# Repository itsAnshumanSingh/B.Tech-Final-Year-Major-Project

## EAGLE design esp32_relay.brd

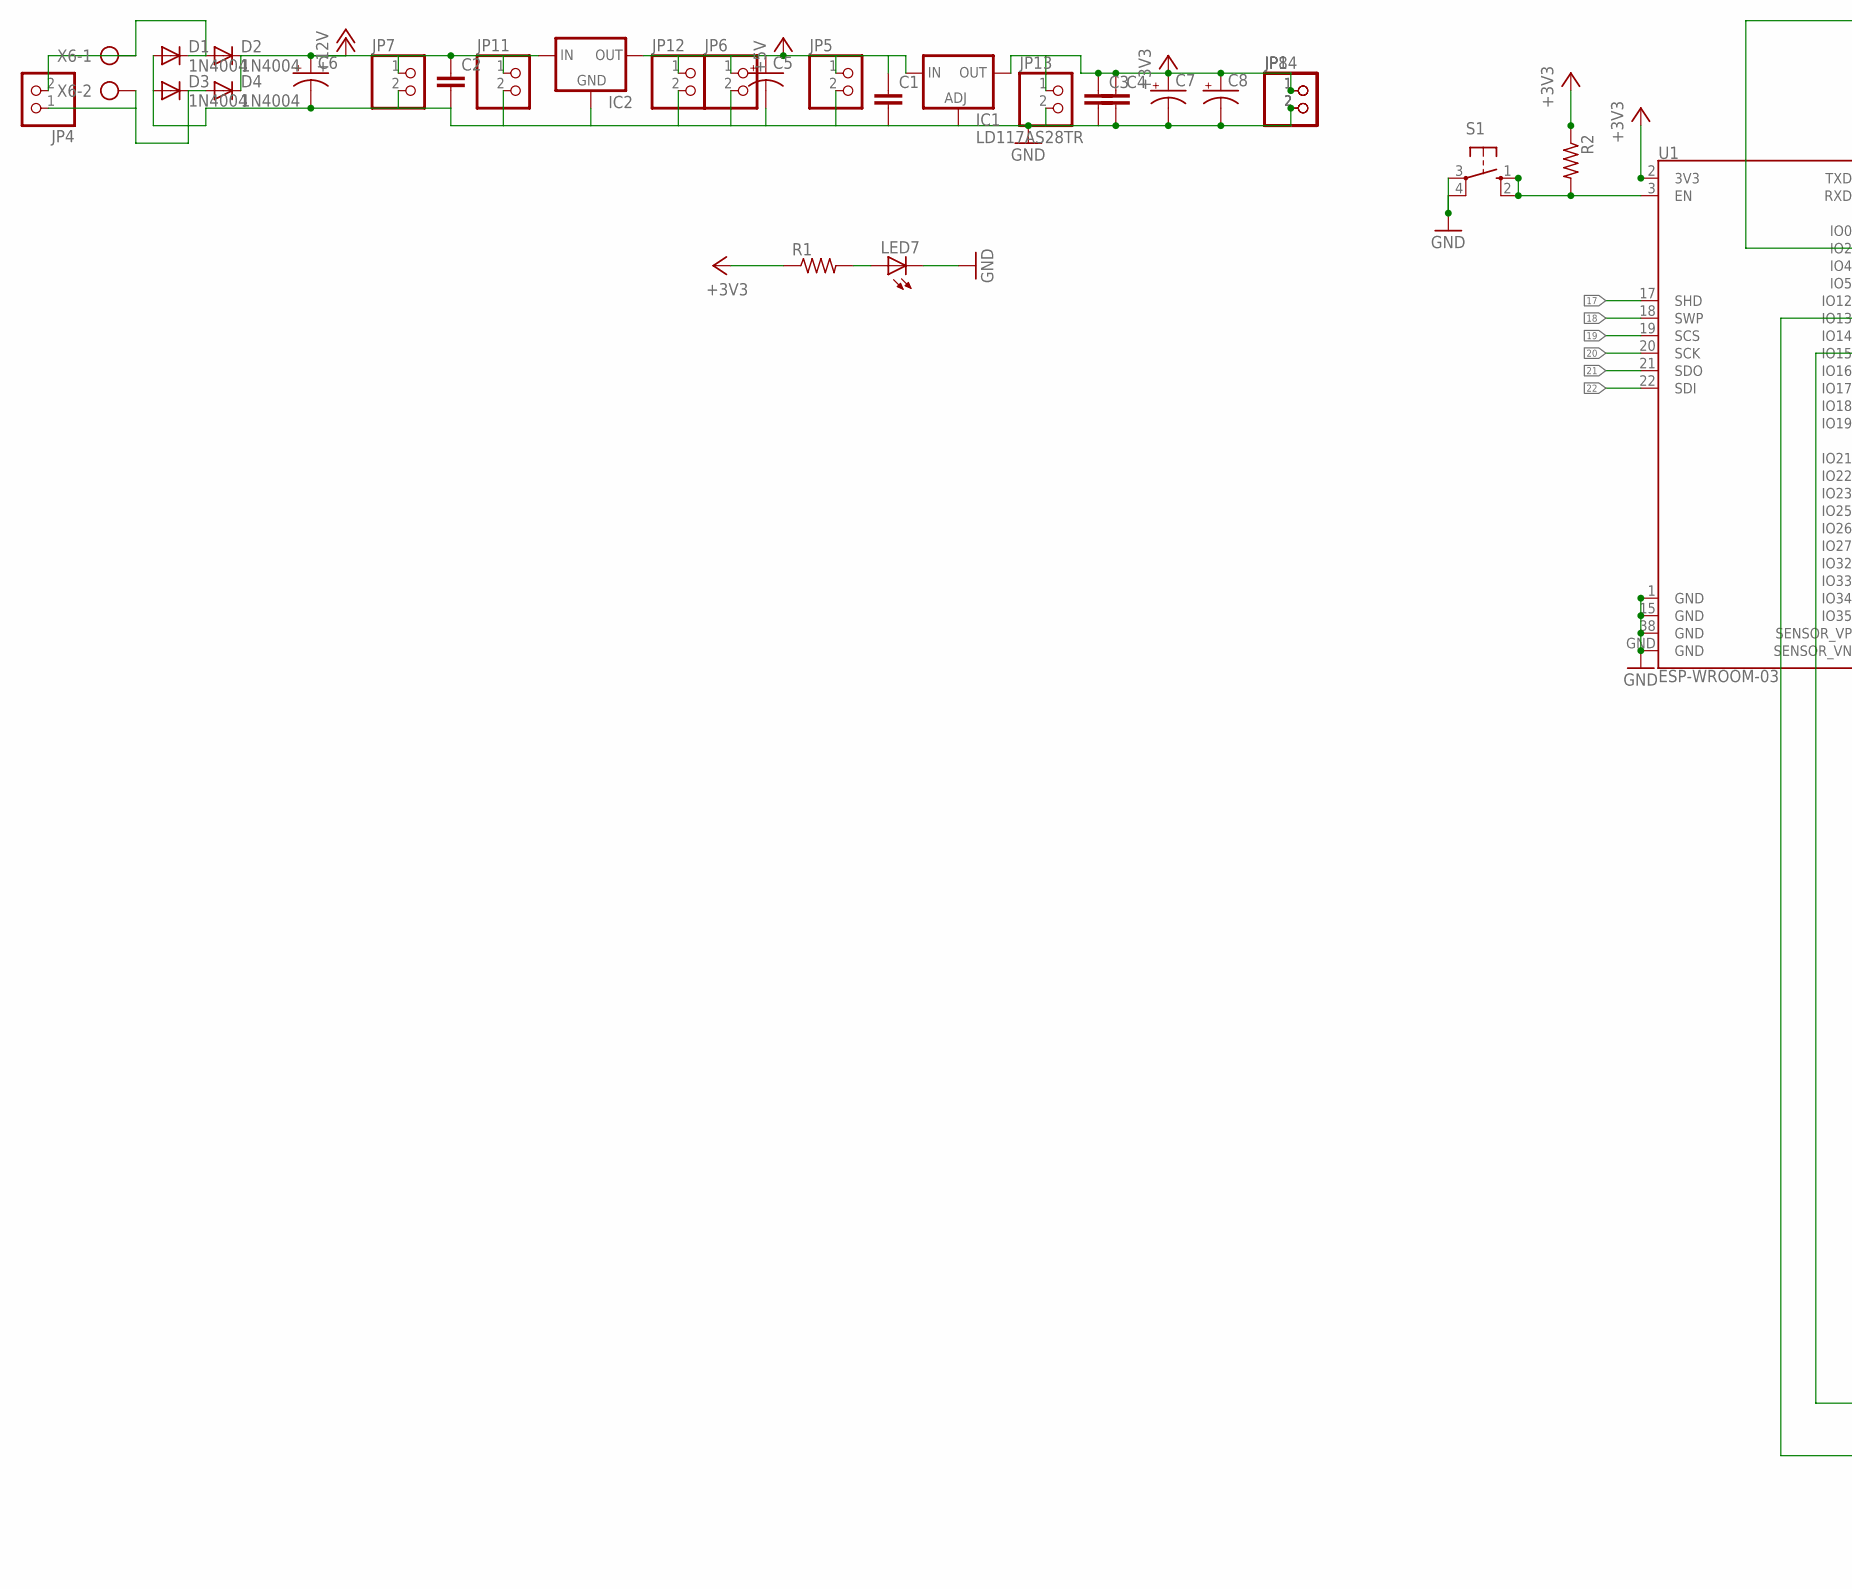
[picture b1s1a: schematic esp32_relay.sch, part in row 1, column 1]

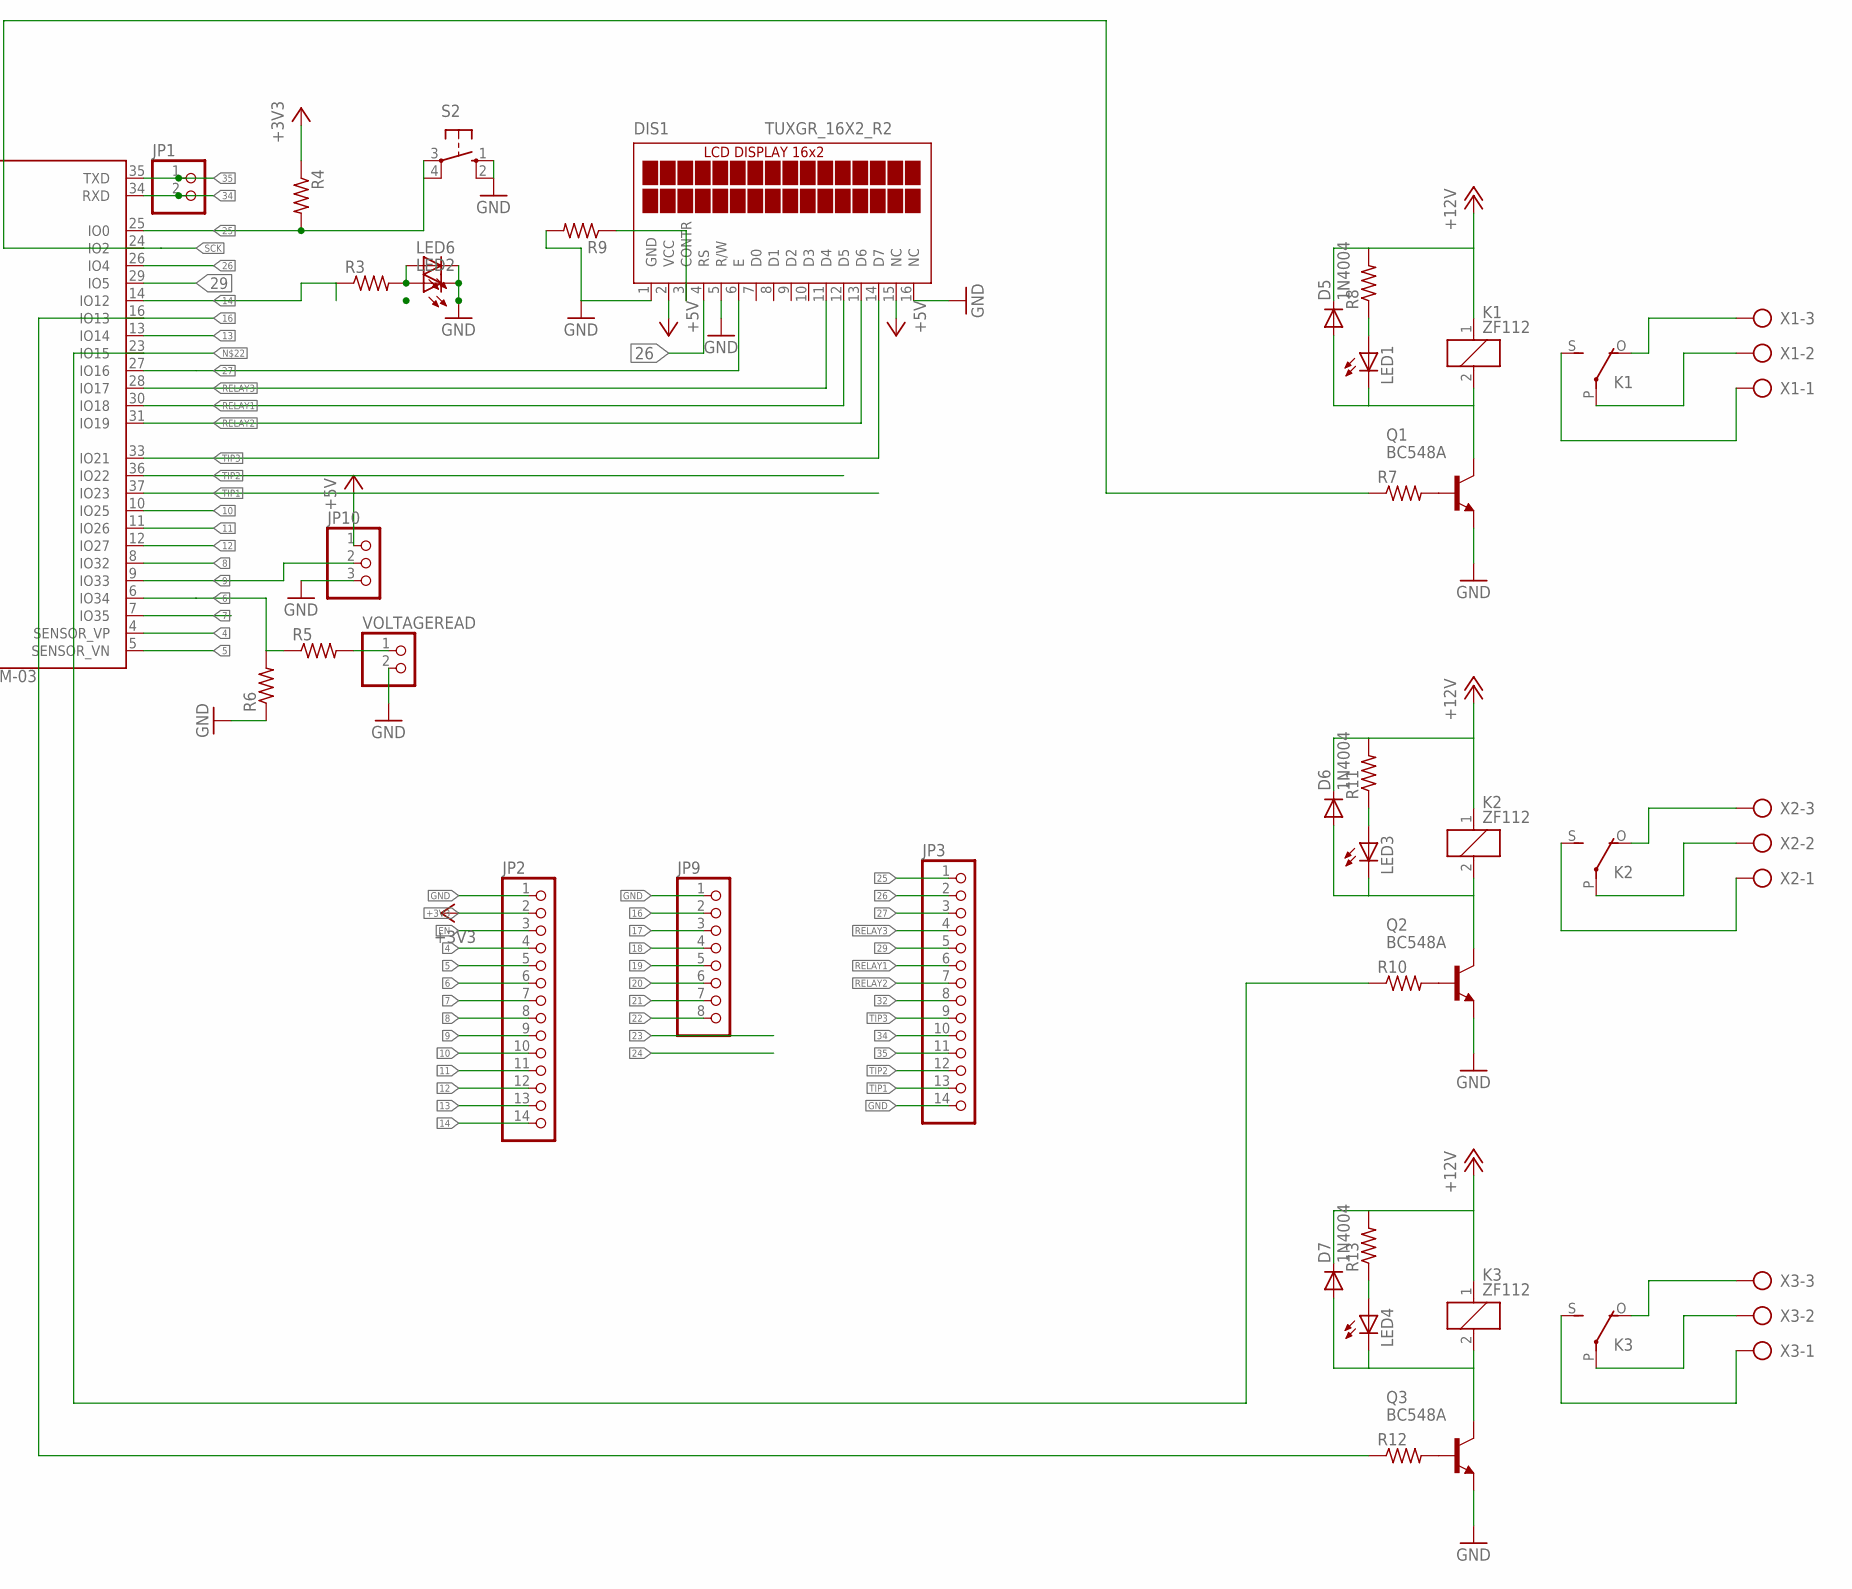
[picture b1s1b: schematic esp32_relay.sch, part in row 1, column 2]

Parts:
C1, C2, C3, C4: C-EUC1206; C1206
C5, C6, C8: CPOL-USE2.5-7; E2,5-7
C7: CPOL-USE2.5-6; E2,5-6
D1, D2, D3, D4, D5, D6, D7: 1N4004; DO41-10
DIS1: TUXGR_16X2_R2
IC1: LD117AS28TR; SOT223
IC2: 78XXL
JP1, JP4, JP5, JP6, JP7, JP8, JP11, JP12, JP13, JP14: PINHD-1X2; 1X02
JP2, JP3: PINHD-1X14; 1X14
JP9: PINHD-1X8; 1X08
JP10: PINHD-1X3; 1X03
K1, K2, K3: ZF112
LED1, LED3, LED4, LED6, LED7: LED3MM
LED2: LEDCHIPLED_1206; CHIPLED_1206
Q1, Q2, Q3: BC548A; TO92-EBC
R1, R2, R3, R4, R5, R6, R7, R8, R9, R10, R11, R13: R-US_0207/7; 0207/7
R12: R-US_0207/10; 0207/10
S1, S2: 10-XX; B3F-10XX
U1: ESP-WROOM-03
VOLTAGEREAD: PINHD-1X2; 1X02
X1, X2, X3: AK500/3-H
X6: AK500/2-H

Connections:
4: JP2.4, U1.4 (SENSOR_VP)
5: JP2.5, U1.5 (SENSOR_VN)
6: JP2.6, R5.1, R6.2, U1.6 (IO34)
7: JP2.7, U1.7 (IO35)
8: JP2.8, U1.8 (IO32)
9: JP2.9, JP10.2, U1.9 (IO33)
10: JP2.10, U1.10 (IO25)
11: JP2.11, U1.11 (IO26)
12: JP2.12, U1.12 (IO27)
13: JP2.13, U1.13 (IO14)
14: JP2.14, R3.1, U1.14 (IO12)
16: JP9.2, R12.1, U1.16 (IO13)
17: JP9.3, U1.17 (SHD)
18: JP9.4, U1.18 (SWP)
19: JP9.5, U1.19 (SCS)
20: JP9.6, U1.20 (SCK)
21: JP9.7, U1.21 (SDO)
22: JP9.8, U1.22 (SDI)
25: JP3.1, R4.2, S2.3, S2.4 (P1), U1.25 (IO0)
26: DIS1.4 (RS), JP3.2, U1.26 (IO4)
27: DIS1.6 (E), JP3.3, U1.27 (IO16)
29: JP3.5, U1.29 (IO5)
32: JP3.8
34: JP1.2, JP3.10, U1.34 (RXD)
35: JP1.1, JP3.11, U1.35 (TXD)
+3V3: C3.1, C4.1, C7.+, C8.+, IC1.4 (OUT), JP2.2, JP8.1, JP13.1, JP14.1, R1.1, R2.1, R4.1, U1.2 (3V3)
+5V: C1.1, C5.+, DIS1.2 (VCC), DIS1.15 (NC), IC1.3 (IN), IC2.OUT, JP5.1, JP6.1, JP10.1, JP12.1
+12V: C2.1, C6.+, D2.C, D4.C, D5.C, D6.C, D7.C, IC2.IN, JP7.1, JP11.1, K1.1, K2.1, K3.1, R8.2, R11.2, R13.2
EN: JP2.3, R2.2, S1.1 (S), S1.2 (S1), U1.3 (EN)
GND: C1.2, C2.2, C3.2, C4.2, C5.-, C6.-, C7.-, C8.-, D1.A, D3.A, DIS1.1 (GND), DIS1.5 (R/W), DIS1.16 (NC), IC1.1 (ADJ), IC2.GND, JP2.1, JP3.14, JP5.2, JP6.2, JP7.2, JP8.2, JP9.1, JP10.3, JP11.2, JP12.2, JP13.2, JP14.2, LED2.C, LED6.K (C), LED7.K (C), Q1.E, Q2.E, Q3.E, R6.1, R9.2, S1.3, S1.4 (P1), S2.1 (S), S2.2 (S1), U1.1 (GND), U1.15 (GND), U1.38 (GND), U1.GND, VOLTAGEREAD.2
unnamed: LED7.A, R1.2
unnamed: D3.C, D4.A, JP4.1, X6.2
unnamed: Q1.B, R7.2
unnamed: R5.2, VOLTAGEREAD.1
unnamed: D5.A, K1.2, LED1.K (C), Q1.C
unnamed: K1.P, X1.2
unnamed: LED2.A, LED6.A, R3.2
unnamed: K1.O, X1.3
unnamed: D1.C, D2.A, JP4.2, X6.1
unnamed: K1.S, X1.1
unnamed: LED1.A, R8.1
unnamed: DIS1.3 (CONTR), R9.1
unnamed: R10.1, U1.23 (IO15)
unnamed: Q2.B, R10.2
unnamed: D6.A, K2.2, LED3.K (C), Q2.C
unnamed: K2.P, X2.2
unnamed: K2.O, X2.3
unnamed: K2.S, X2.1
unnamed: LED3.A, R11.1
unnamed: Q3.B, R12.2
unnamed: D7.A, K3.2, LED4.K (C), Q3.C
unnamed: K3.P, X3.2
unnamed: K3.O, X3.3
unnamed: K3.S, X3.1
unnamed: LED4.A, R13.1
RELAY1: DIS1.12 (D5), JP3.6, U1.30 (IO18)
RELAY2: DIS1.13 (D6), JP3.7, U1.31 (IO19)
RELAY3: DIS1.11 (D4), JP3.4, U1.28 (IO17)
SCK: R7.1, U1.24 (IO2)
TIP1: JP3.13, U1.37 (IO23)
TIP2: JP3.12, U1.36 (IO22)
TIP3: DIS1.14 (D7), JP3.9, U1.33 (IO21)

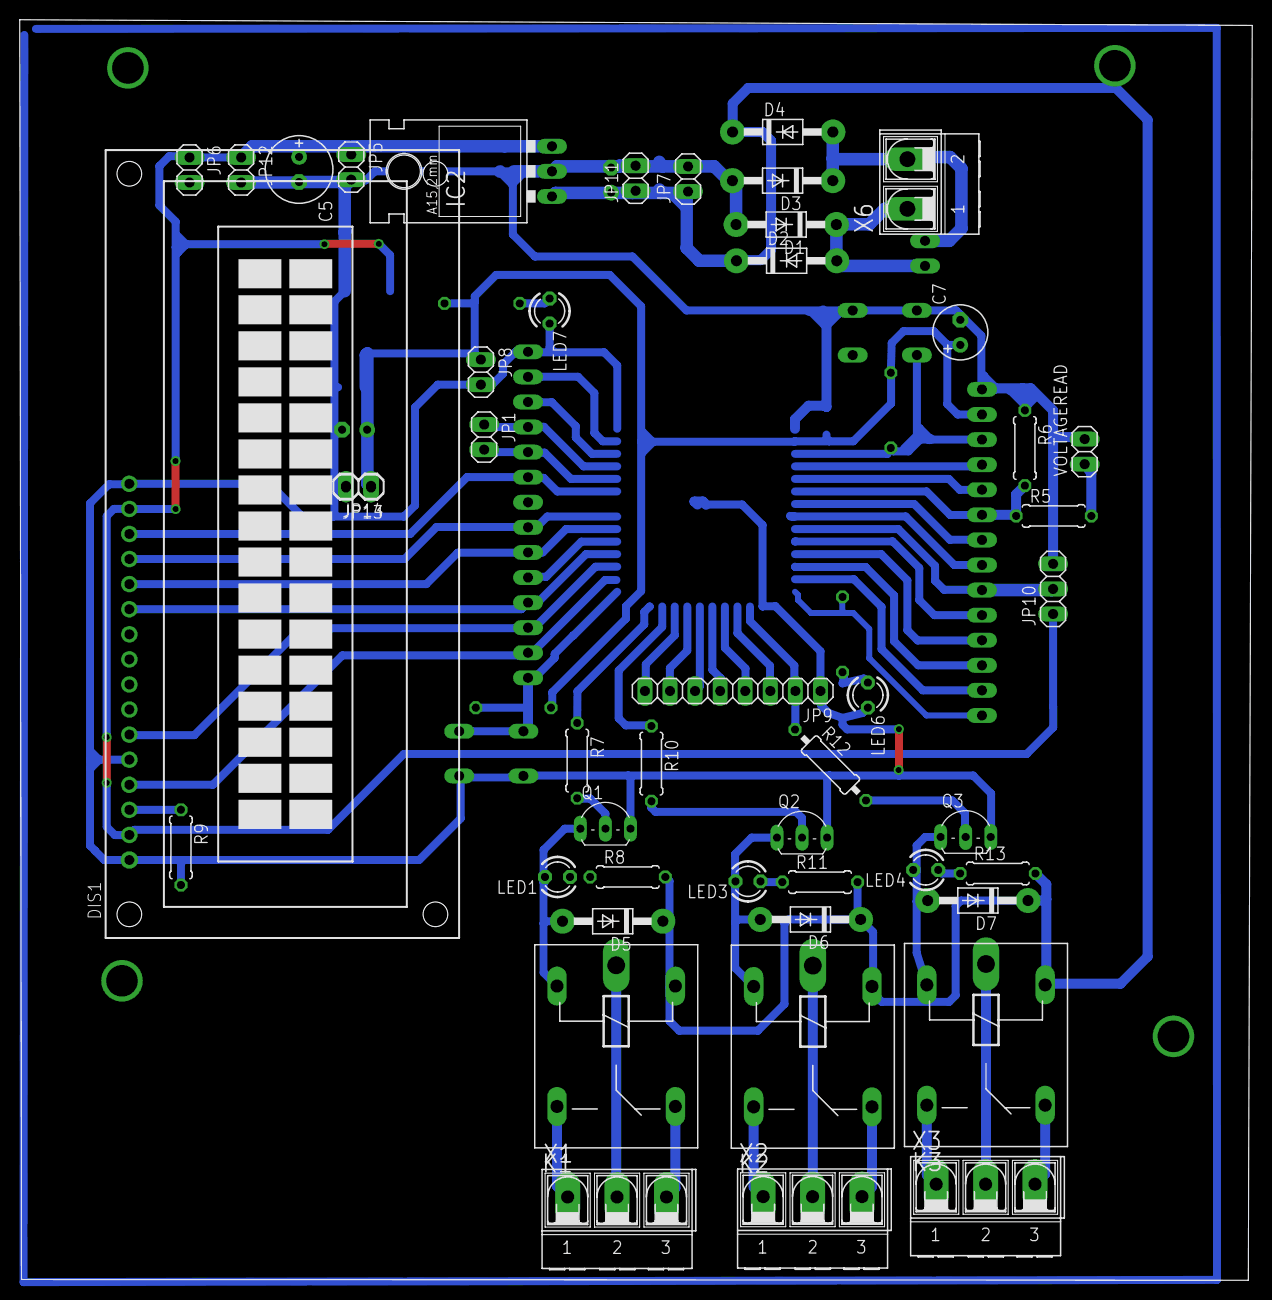
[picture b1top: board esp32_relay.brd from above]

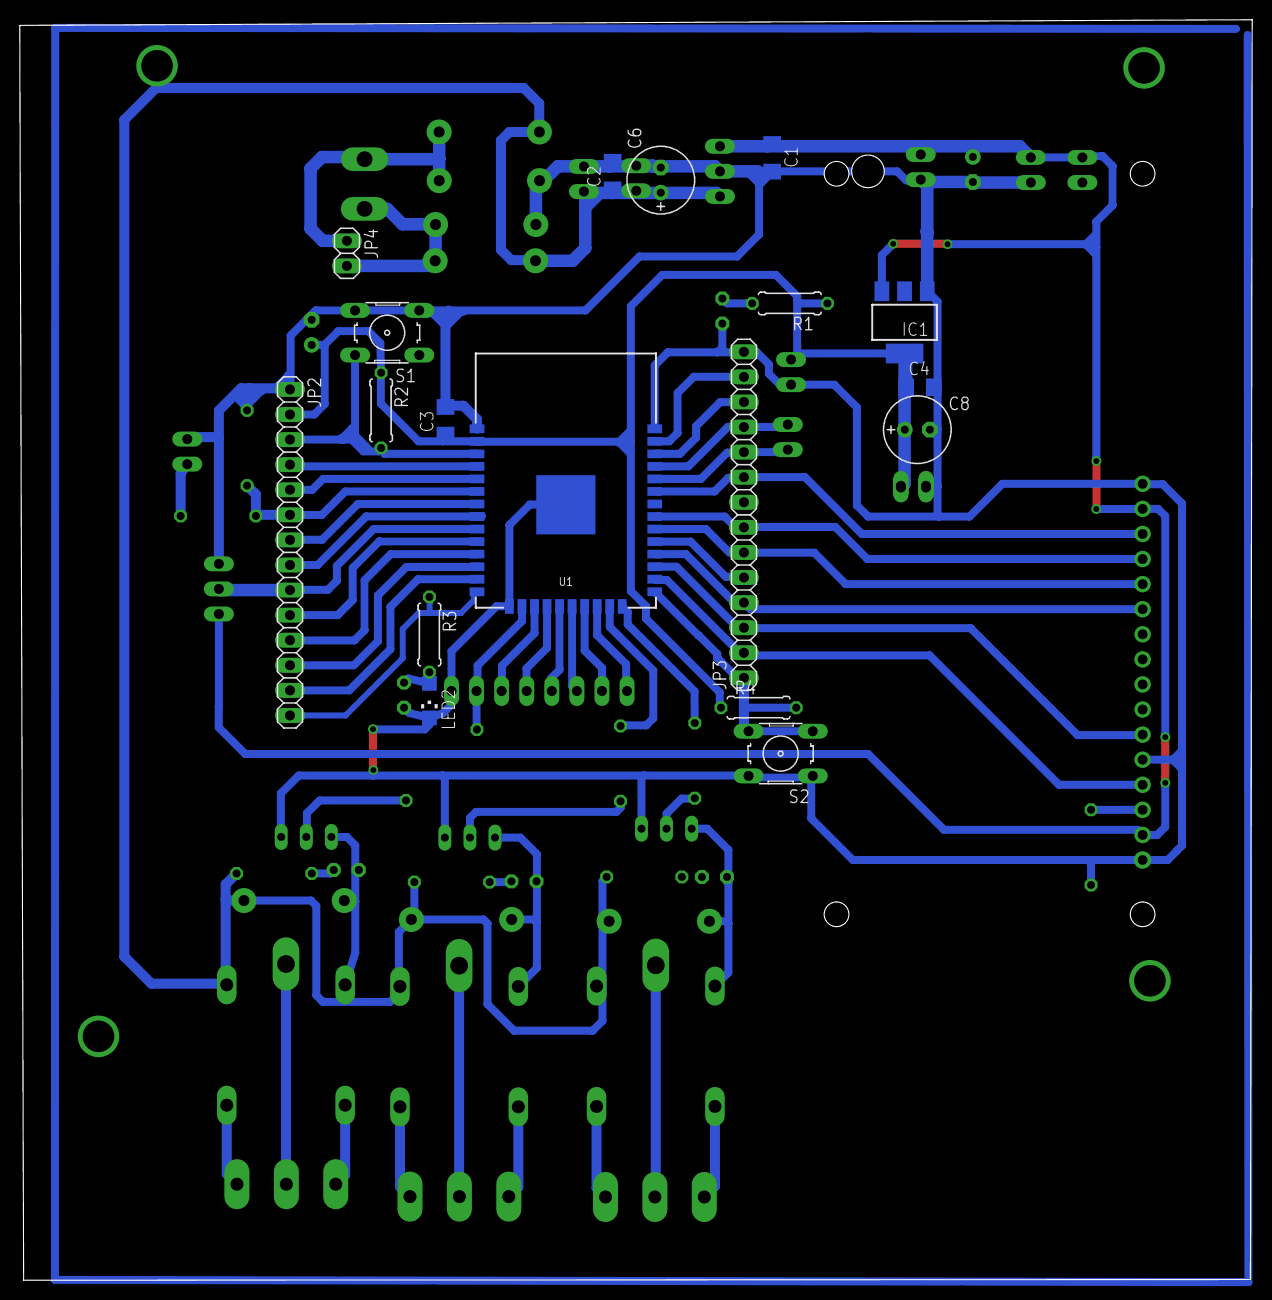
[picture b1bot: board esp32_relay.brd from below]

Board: 2 copper layers, 124.8 x 127.7 mm, 65 parts (18 on the bottom side), 61 nets.
